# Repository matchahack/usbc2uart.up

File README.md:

# about

This project enable the user to connect and read/write their UART signals via USBC.

Feel free to read more about the design and use process [here](https://substack.com/home/post/p-186289458)

## PCB electronics design

In [`TOP-V2`](./TOP-V2), the KiCad files for the project schematic and layout are available, which enable BOM, Gerber, and Centroid generation for manufacture and assembly.

> [!NOTE]
> The footprint paths will need to be changed for correct imports

Also the footprints and revelent 3D models needed to generate `.step` files for freeCAD housing design...

## PCB 3D-printed enclosure

In [`ENCLOSURE`](./ENCLOSURE), the freeCAD source files that enable us to generate a `.stl` - and therefore enable 3D-printed housing for the PCB

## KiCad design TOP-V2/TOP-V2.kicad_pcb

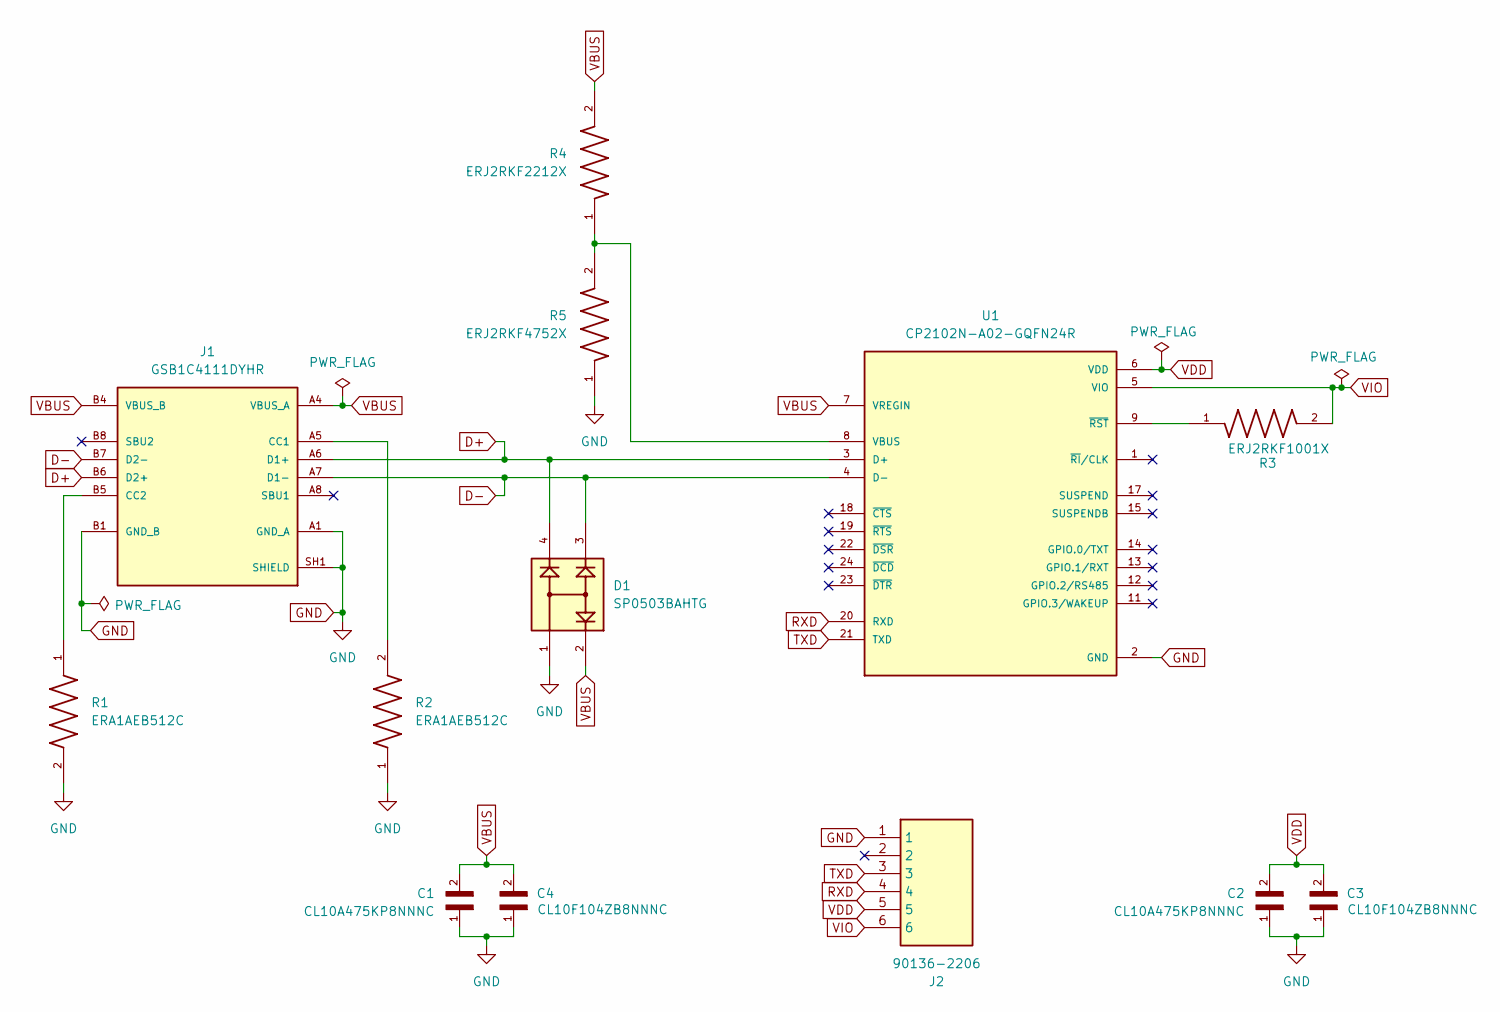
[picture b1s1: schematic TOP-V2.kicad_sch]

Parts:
C1, C2: CL10A475KP8NNNC; CAPC1608X90N; DigiKey_Part_Number 1276-1044-1-ND
C3, C4: CL10F104ZB8NNNC; CAPC1608X90N; DigiKey_Part_Number 1276-1012-1-ND
D1: SP0503BAHTG; SOT143; PARTREV N/A; DigiKey_Part_Number F2715CT-ND
J1: GSB1C4111DYHR; AMPHENOL_GSB1C4111DYHR; PARTREV AX1; DigiKey_Part_Number 664-GSB1C4111DYHRCT-ND
J2: 90136-2206; SHDRRA6W65P0X254_1X6_1859X1090X751P; Manufacturer_Part_Number 90136-2206
R1, R2: ERA1AEB512C; RES_ERA1AEB512C; PARTREV 3/1/2020; DigiKey_Part_Number 10-ERA-1AEB512CCT-ND
R3: ERJ2RKF1001X; RES_ERJ2RKF1001X; PARTREV 3/1/2020; DigiKey_Part_Number P1.00KLCT-ND
R4: ERJ2RKF2212X; RES_ERJ2RKF2212X; PARTREV 3/1/2020; DigiKey_Part_Number P22.1KLCT-ND
R5: ERJ2RKF4752X; RES_ERJ2RKF4752X; PARTREV 3/1/2020; DigiKey_Part_Number P47.5KLCT-ND
U1: CP2102N-A02-GQFN24R; QFN50P400X400X80-25N; PARTREV 1.3; DigiKey_Part_Number 336-5888-1-ND

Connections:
D+: D1.4, J1.A6 (D1+), J1.B6 (D2+), U1.3 (D+)
D-: D1.3, J1.A7 (D1-), J1.B7 (D2-), U1.4 (D-)
GND: C1.1, C2.1, C3.1, C4.1, D1.1, J1.A1 (GND_A), J1.A12 (GND_A), J1.B1 (GND_B), J1.B12 (GND_B), J1.SH1 (SHIELD), J1.SH2 (SHIELD), J1.SH3 (SHIELD), J1.SH4 (SHIELD), J2.1, R1.2, R2.1, R5.1, U1.2 (GND), U1.25 (GND)
unnamed: J1.A5 (CC1), R2.2
unnamed: J1.B5 (CC2), R1.1
unnamed: R4.1, R5.2, U1.8 (VBUS)
unnamed: R3.1, U1.9 (~RST)
RXD: J2.4, U1.20 (RXD)
TXD: J2.3, U1.21 (TXD)
VBUS: C1.2, C4.2, D1.2, J1.A4 (VBUS_A), J1.A9 (VBUS_A), J1.B4 (VBUS_B), J1.B9 (VBUS_B), R4.2, U1.7 (VREGIN)
VDD: C2.2, C3.2, J2.5, U1.6 (VDD)
VIO: J2.6, R3.2, U1.5 (VIO)

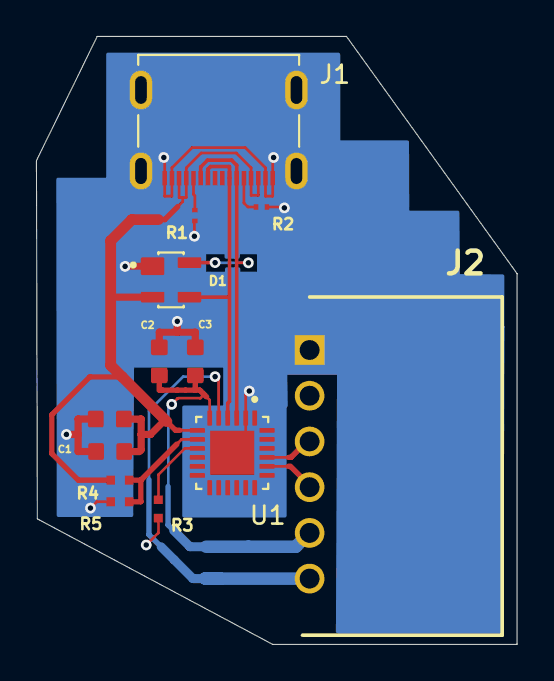
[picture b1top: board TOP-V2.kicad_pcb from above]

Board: 2 copper layers, 26.7 x 33.8 mm, 13 parts (0 on the bottom side), 12 nets.

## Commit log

2026-02-07 init
2026-02-07 add readme
2026-02-09 images
2026-02-10 packaged
2026-02-10 substack link
2026-02-17 Note
